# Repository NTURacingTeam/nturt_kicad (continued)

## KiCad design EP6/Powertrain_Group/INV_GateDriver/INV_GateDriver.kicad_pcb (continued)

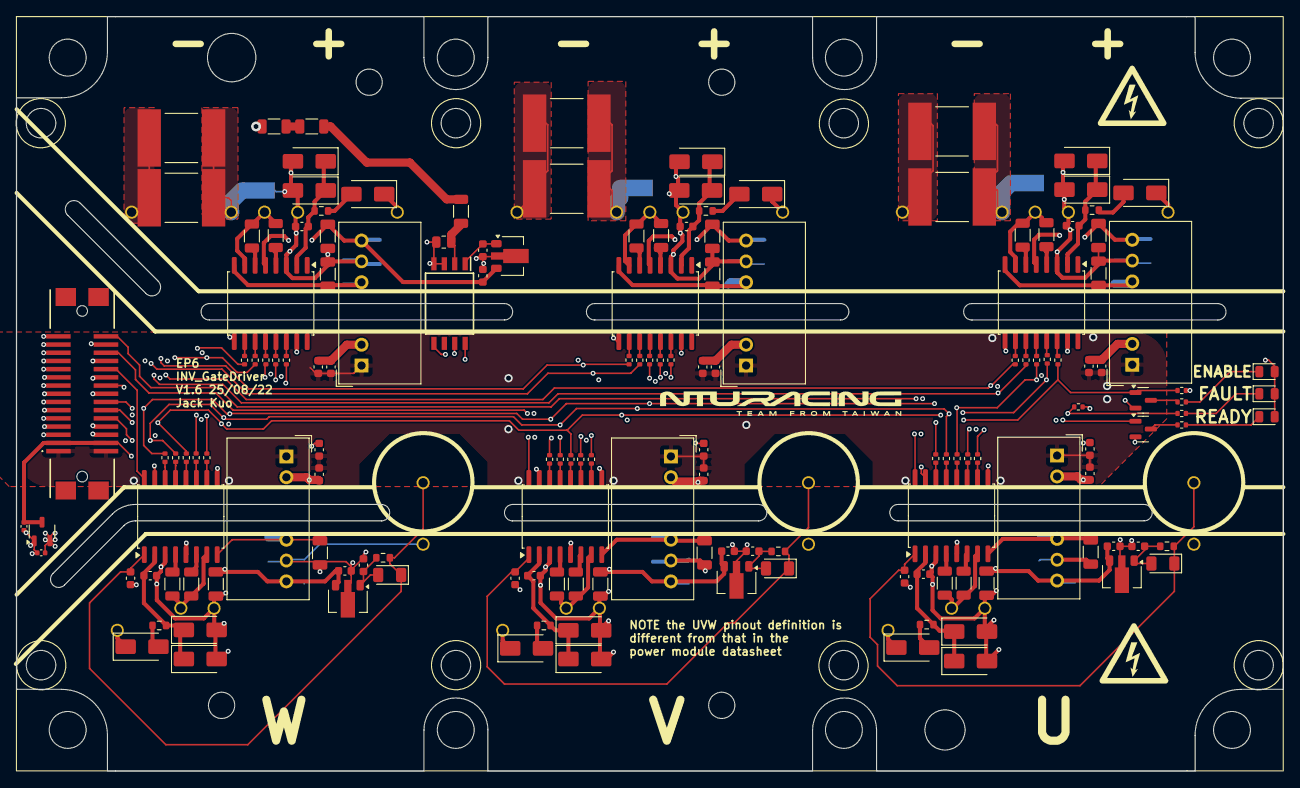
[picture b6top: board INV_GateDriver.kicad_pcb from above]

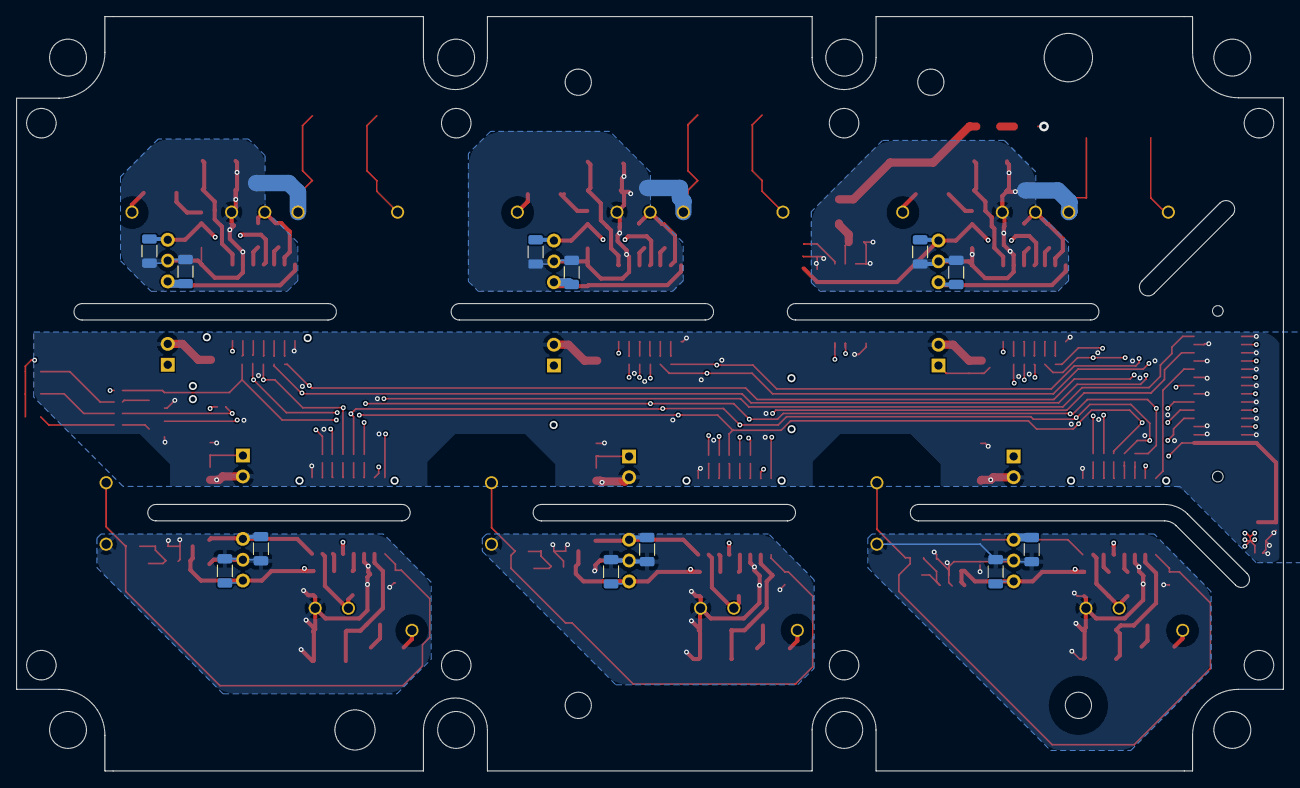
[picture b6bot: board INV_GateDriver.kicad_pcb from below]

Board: 4 copper layers, 154.5 x 92.0 mm, 174 parts (15 on the bottom side), 122 nets.

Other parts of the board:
R17, R18, R24, R25, R28, R29, R35, R36: CRCW080510R0FKEAHP; R_1206_3216Metric

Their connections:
/GateDriverNodeU/G_H: R28.1, R29.2; also elsewhere on the board
/GateDriverNodeU/G_L: R35.1, R36.2; also elsewhere on the board
/GateDriverNodeV/G_H: R17.1, R18.2; also elsewhere on the board
/GateDriverNodeV/G_L: R24.1, R25.2; also elsewhere on the board
unnamed 103: R17.2; also elsewhere on the board
unnamed 104: R18.1; also elsewhere on the board
unnamed 110: R24.2; also elsewhere on the board
unnamed 111: R25.1; also elsewhere on the board
unnamed 117: R28.2; also elsewhere on the board
unnamed 118: R29.1; also elsewhere on the board
unnamed 124: R35.2; also elsewhere on the board
unnamed 125: R36.1; also elsewhere on the board

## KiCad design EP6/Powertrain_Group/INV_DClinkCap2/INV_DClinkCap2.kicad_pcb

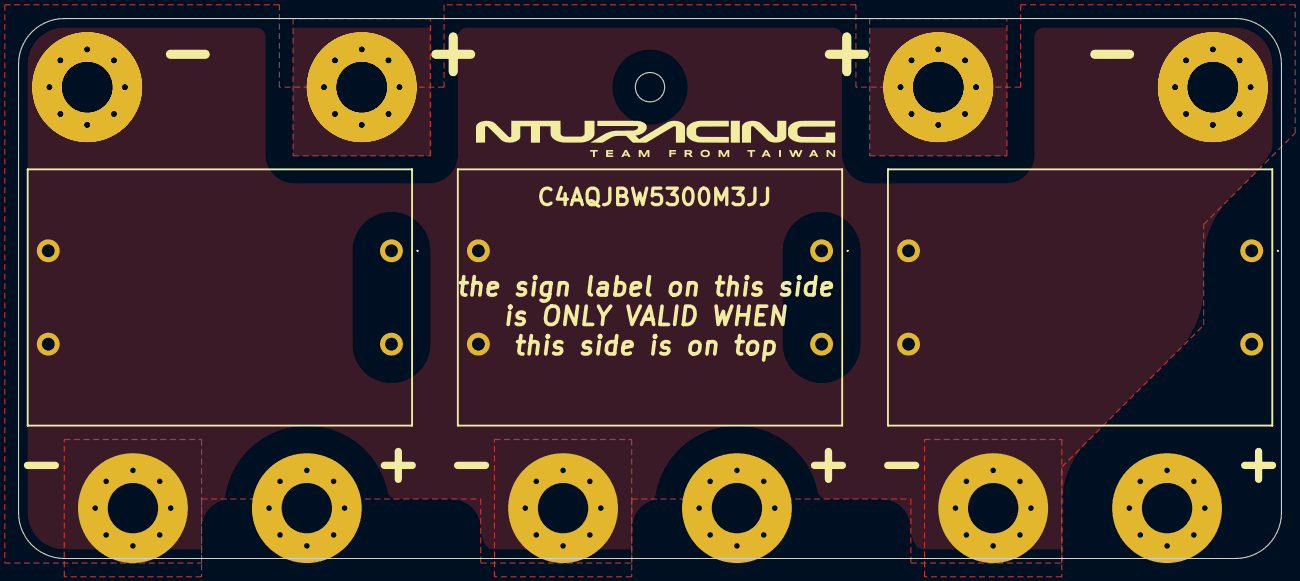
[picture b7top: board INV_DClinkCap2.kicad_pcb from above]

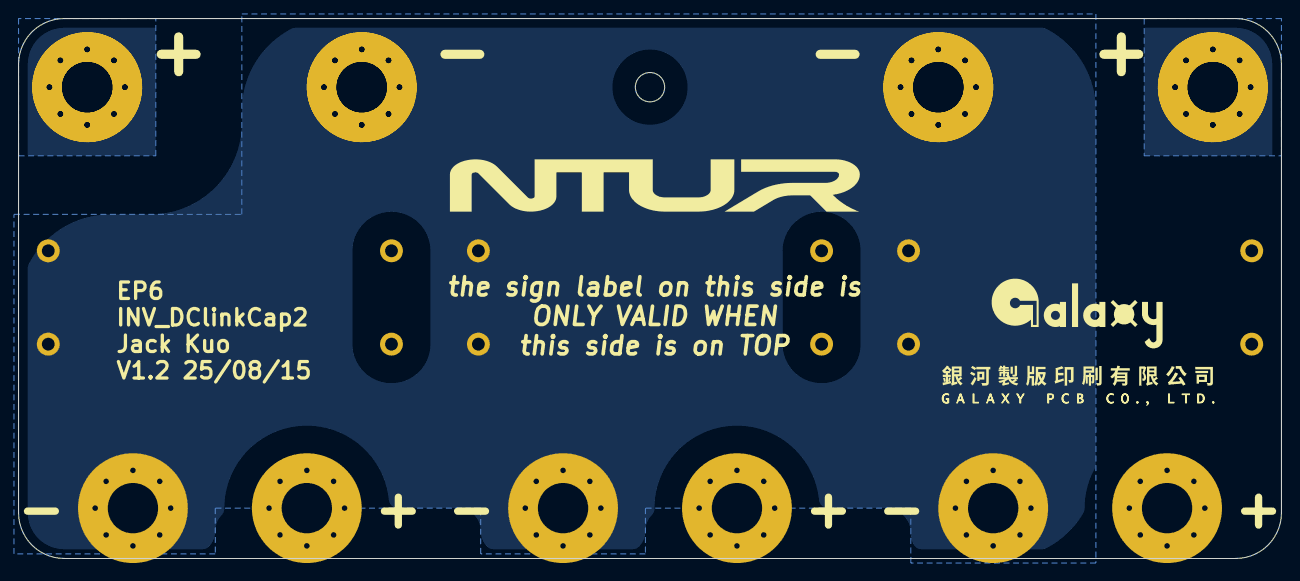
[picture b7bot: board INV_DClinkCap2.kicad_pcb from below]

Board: 2 copper layers, 138.0 x 59.0 mm, 18 parts (7 on the bottom side), 2 nets, no tracks yet.

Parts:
C1, C3, C5: 30µF; C4AQJBW5300M3JJ
H1, H3, H5, H8, H8#2, H10, H10#2: HV-; MountingHole_5.5mm_Pad_Via_15mm_square
H2, H4, H6, H7, H7#2, H9, H9#2: HV+; MountingHole_5.5mm_Pad_Via_15mm_square
H11: MountingHole; MountingHole_3.2mm_M3

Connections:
HV+: C1.1, C3.1, C5.1, H2.1, H4.1, H6.1, H7.1, H7#2.1, H9.1, H9#2.1
HV-: C1.2, C3.2, C5.2, H1.1, H3.1, H5.1, H8.1, H8#2.1, H10.1, H10#2.1

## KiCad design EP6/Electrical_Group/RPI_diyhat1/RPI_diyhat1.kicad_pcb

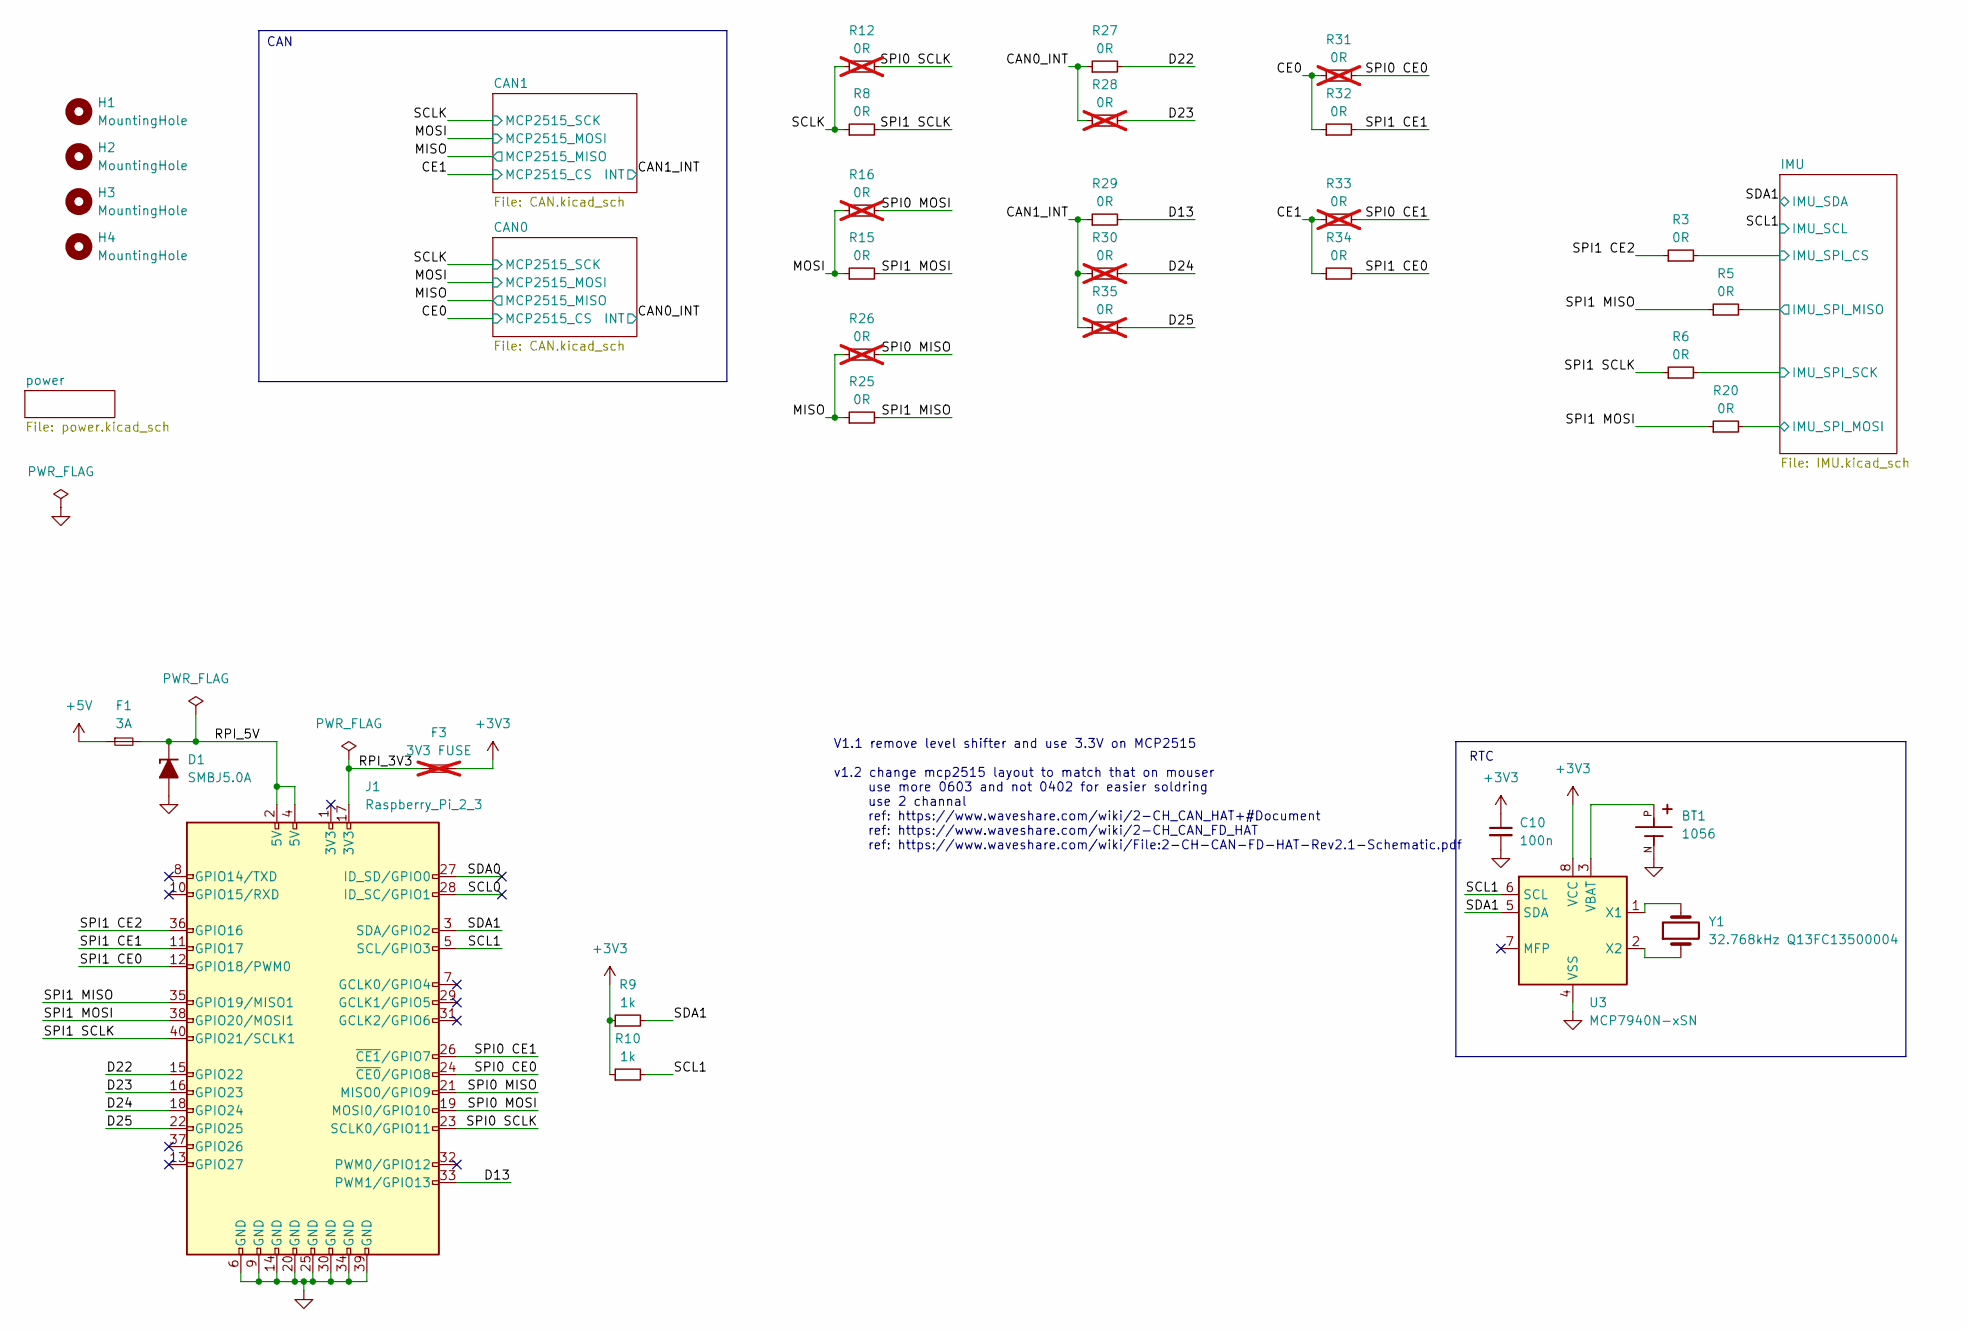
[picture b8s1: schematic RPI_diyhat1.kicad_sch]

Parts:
BT1: 1056; BAT_1056; PARTREV D
C10: 100n; C_0603_1608Metric
D1: SMBJ5.0A; D_SMB
F1: 3A; Fuse_1206_3216Metric
F3: 3V3 FUSE; Fuse_1206_3216Metric; not fitted
H1, H2, H3, H4: MountingHole; MountingHole_2.7mm_M2.5
J1: Raspberry_Pi_2_3; PinSocket_2x20_P2.54mm_Vertical
R3, R5, R6, R8, R15, R20, R25, R27, R29, R32, R34: 0R; R_0603_1608Metric
R9, R10: 1k; R_0603_1608Metric
R12, R16, R26, R28, R30, R31, R33, R35: 0R; R_0603_1608Metric; not fitted
U3: MCP7940N-xSN; SOIC-8_3.9x4.9mm_P1.27mm
Y1: 32.768kHz Q13FC13500004; Crystal_SMD_3215-2Pin_3.2x1.5mm

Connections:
+3V3: C10.1, F3.2, R9.1, R10.1, U3.8 (VCC); also elsewhere on the board
+5V: F1.1; also elsewhere on the board
/CAN0_INT: R27.1, R28.1; also elsewhere on the board
/CAN1_INT: R29.1, R30.1, R35.1; also elsewhere on the board
/CE0: R31.1, R32.1; also elsewhere on the board
/CE1: R33.1, R34.1; also elsewhere on the board
/D13: J1.33 (PWM1/GPIO13), R29.2
/D22: J1.15 (GPIO22), R27.2
/D23: J1.16 (GPIO23), R28.2
/D24: J1.18 (GPIO24), R30.2
/D25: J1.22 (GPIO25), R35.2
/IMU/IMU_SPI_CS: R3.2; also elsewhere on the board
/IMU/IMU_SPI_MISO: R5.2; also elsewhere on the board
/IMU/IMU_SPI_MOSI: R20.2; also elsewhere on the board
/IMU/IMU_SPI_SCK: R6.2; also elsewhere on the board
/MISO: R25.1, R26.1; also elsewhere on the board
/MOSI: R15.1, R16.1; also elsewhere on the board
/RPI_3V3: F3.1, J1.17 (3V3)
/RPI_5V: D1.1 (K), F1.2, J1.2 (5V), J1.4 (5V)
/SCL0: J1.28 (ID_SC/GPIO1)
/SCL1: J1.5 (SCL/GPIO3), R10.2, U3.6 (SCL); also elsewhere on the board
/SCLK: R8.1, R12.1; also elsewhere on the board
/SDA0: J1.27 (ID_SD/GPIO0)
/SDA1: J1.3 (SDA/GPIO2), R9.2, U3.5 (SDA); also elsewhere on the board
/SPI0 CE0: J1.24 (~CE0/GPIO8), R31.2
/SPI0 CE1: J1.26 (~CE1/GPIO7), R33.2
/SPI0 MISO: J1.21 (MISO0/GPIO9), R26.2
/SPI0 MOSI: J1.19 (MOSI0/GPIO10), R16.2
/SPI0 SCLK: J1.23 (SCLK0/GPIO11), R12.2
/SPI1 CE0: J1.12 (GPIO18/PWM0), R34.2
/SPI1 CE1: J1.11 (GPIO17), R32.2
/SPI1 CE2: J1.36 (GPIO16), R3.1
/SPI1 MISO: J1.35 (GPIO19/MISO1), R5.1, R25.2
/SPI1 MOSI: J1.38 (GPIO20/MOSI1), R15.2, R20.1
/SPI1 SCLK: J1.40 (GPIO21/SCLK1), R6.1, R8.2
GND: BT1.N, C10.2, D1.2 (A), J1.6 (GND), J1.9 (GND), J1.14 (GND), J1.20 (GND), J1.25 (GND), J1.30 (GND), J1.34 (GND), J1.39 (GND), U3.4 (VSS); also elsewhere on the board
unnamed: BT1.P, U3.3 (VBAT)
unnamed: U3.1 (X1), Y1.2
unnamed: U3.2 (X2), Y1.1

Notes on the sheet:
RTC
CAN
V1.1 remove level shifter and use 3.3V on MCP2515 v1.2 change mcp2515 layout to match that on mouser use more 0603 and not 0402 for easier soldring use 2 channal ref: https://www.waveshare.com/wiki/2-CH_CAN_HAT+#Document ref: https://www.waveshare.com/wiki/2-CH_CAN_FD_HAT ref: https://www.waveshare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

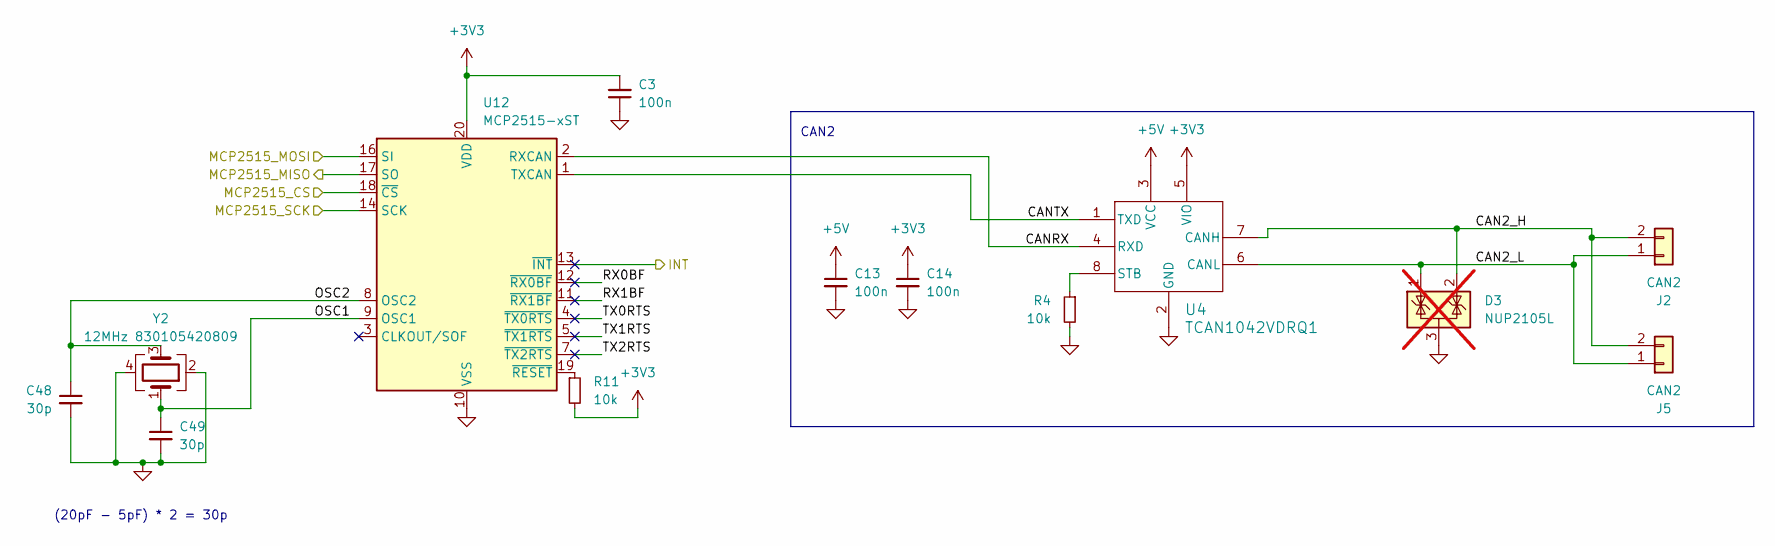
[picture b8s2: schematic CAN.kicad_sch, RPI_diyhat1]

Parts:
C3, C13, C14: 100n; C_0603_1608Metric
C48, C49: 30p; C_0603_1608Metric
D3: NUP2105L; SOT-23; not fitted
J2, J5: CAN2; JST_XH_B2B-XH-A_1x02_P2.50mm_Vertical
R4: 10k; C_0603_1608Metric
R11: 10k; R_0603_1608Metric
U4: TCAN1042VDRQ1; SOIC-8_3.9x4.9mm_P1.27mm
U12: MCP2515-xST; TSSOP-20_4.4x6.5mm_P0.65mm
Y2: 12MHz 830105420809; Crystal_SMD_3225-4Pin_3.2x2.5mm

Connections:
+3V3: C3.2, C14.1, R11.2, U4.5 (VIO), U12.20 (VDD); also elsewhere on the board
+5V: C13.1, U4.3 (VCC); also elsewhere on the board
/CAN1/CAN2_H: D3.2 (K), J2.2, J5.2, U4.7 (CANH)
/CAN1/CAN2_L: D3.1 (K), J2.1, J5.1, U4.6 (CANL)
/CAN1/CANRX: U4.4 (RXD), U12.2 (RXCAN)
/CAN1/CANTX: U4.1 (TXD), U12.1 (TXCAN)
/CAN1/OSC1: C49.1, U12.9 (OSC1), Y2.1
/CAN1/OSC2: C48.1, U12.8 (OSC2), Y2.3
/CAN1/RX0BF: U12.12 (~RX0BF)
/CAN1/RX1BF: U12.11 (~RX1BF)
/CAN1/TX0RTS: U12.4 (~TX0RTS)
/CAN1/TX1RTS: U12.5 (~TX1RTS)
/CAN1/TX2RTS: U12.7 (~TX2RTS)
/CAN1_INT: U12.13 (~INT); also elsewhere on the board
/CE1: U12.18 (~CS); also elsewhere on the board
/MISO: U12.17 (SO); also elsewhere on the board
/MOSI: U12.16 (SI); also elsewhere on the board
/SCLK: U12.14 (SCK); also elsewhere on the board
GND: C3.1, C13.2, C14.2, C48.2, C49.2, D3.3 (A), R4.2, U4.2 (GND), U12.10 (VSS), Y2.2, Y2.4; also elsewhere on the board
unnamed: R4.1, U4.8 (STB)
unnamed: R11.1, U12.19 (~RESET)

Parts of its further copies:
C2, C34, C35: 100n; C_0603_1608Metric
C50, C51: 30p; C_0603_1608Metric
D8: NUP2105L; SOT-23; not fitted
J6, J7: CAN2; JST_XH_B2B-XH-A_1x02_P2.50mm_Vertical
R17: 10k; R_0603_1608Metric
R18: 10k; C_0603_1608Metric
U8: TCAN1042VDRQ1; SOIC-8_3.9x4.9mm_P1.27mm
U13: MCP2515-xST; TSSOP-20_4.4x6.5mm_P0.65mm
Y3: 12MHz 830105420809; Crystal_SMD_3225-4Pin_3.2x2.5mm

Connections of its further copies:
+3V3: C2.2, C35.1, R17.2, U8.5 (VIO), U13.20 (VDD); also elsewhere on the board
+5V: C34.1, U8.3 (VCC); also elsewhere on the board
/CAN0/CAN2_H: D8.2 (K), J6.2, J7.2, U8.7 (CANH)
/CAN0/CAN2_L: D8.1 (K), J6.1, J7.1, U8.6 (CANL)
/CAN0/CANRX: U8.4 (RXD), U13.2 (RXCAN)
/CAN0/CANTX: U8.1 (TXD), U13.1 (TXCAN)
/CAN0/OSC1: C51.1, U13.9 (OSC1), Y3.1
/CAN0/OSC2: C50.1, U13.8 (OSC2), Y3.3
/CAN0/RX0BF: U13.12 (~RX0BF)
/CAN0/RX1BF: U13.11 (~RX1BF)
/CAN0/TX0RTS: U13.4 (~TX0RTS)
/CAN0/TX1RTS: U13.5 (~TX1RTS)
/CAN0/TX2RTS: U13.7 (~TX2RTS)
/CAN0_INT: U13.13 (~INT); also elsewhere on the board
/CE0: U13.18 (~CS); also elsewhere on the board
/MISO: U13.17 (SO); also elsewhere on the board
/MOSI: U13.16 (SI); also elsewhere on the board
/SCLK: U13.14 (SCK); also elsewhere on the board
GND: C2.1, C34.2, C35.2, C50.2, C51.2, D8.3 (A), R18.2, U8.2 (GND), U13.10 (VSS), Y3.2, Y3.4; also elsewhere on the board
unnamed: R18.1, U8.8 (STB)
unnamed: R17.1, U13.19 (~RESET)

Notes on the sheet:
(20pF - 5pF) * 2 = 30p
CAN2

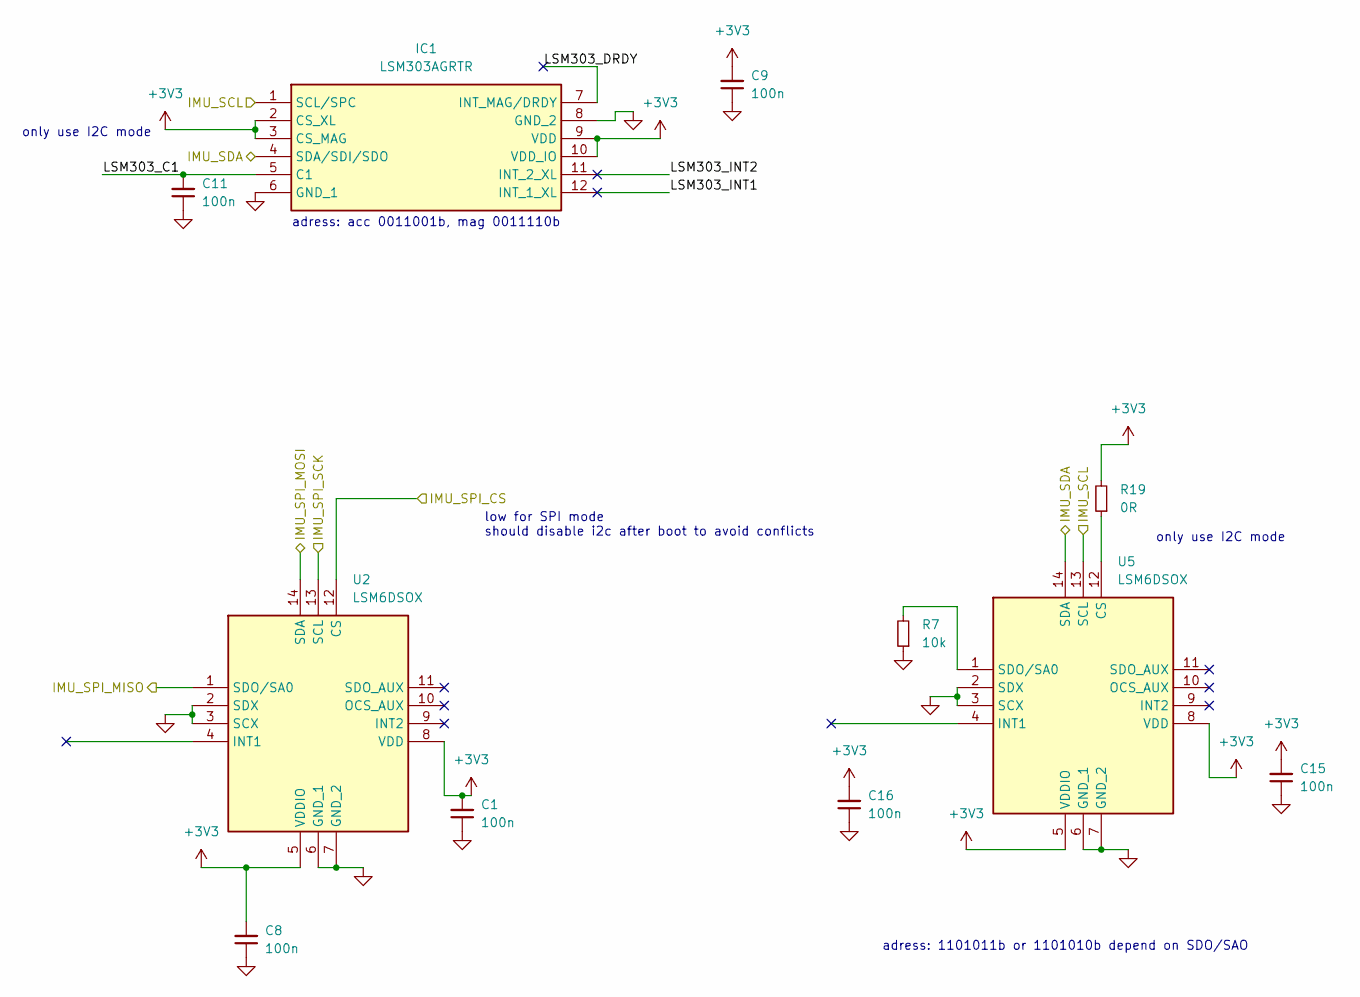
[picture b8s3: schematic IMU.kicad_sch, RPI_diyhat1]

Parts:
C1, C8, C9, C11, C15, C16: 100n; C_0402_1005Metric
IC1: LSM303AGRTR; LGA-12_2x2mm_P0.5mm; Mouser Part Number 511-LSM303AGRTR
R7: 10k; R_0402_1005Metric
R19: 0R; R_0402_1005Metric
U2, U5: LSM6DSOX; LGA-14_3x2.5mm_P0.5mm_LayoutBorder3x4y; Mouser Part Number 511-LSM6DSOXTR

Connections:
+3V3: C1.2, C8.2, C9.2, C15.2, C16.2, IC1.2 (CS_XL), IC1.3 (CS_MAG), IC1.9 (VDD), IC1.10 (VDD_IO), R19.2, U2.5 (VDDIO), U2.8 (VDD), U5.5 (VDDIO), U5.8 (VDD); also elsewhere on the board
/IMU/IMU_SPI_CS: U2.12 (CS); also elsewhere on the board
/IMU/IMU_SPI_MISO: U2.1 (SDO/SA0); also elsewhere on the board
/IMU/IMU_SPI_MOSI: U2.14 (SDA); also elsewhere on the board
/IMU/IMU_SPI_SCK: U2.13 (SCL); also elsewhere on the board
/IMU/LSM303_C1: C11.2, IC1.5 (C1)
/IMU/LSM303_DRDY: IC1.7 (INT_MAG/DRDY)
/IMU/LSM303_INT1: IC1.12 (INT_1_XL)
/IMU/LSM303_INT2: IC1.11 (INT_2_XL)
/SCL1: IC1.1 (SCL/SPC), U5.13 (SCL); also elsewhere on the board
/SDA1: IC1.4 (SDA/SDI/SDO), U5.14 (SDA); also elsewhere on the board
GND: C1.1, C8.1, C9.1, C11.1, C15.1, C16.1, IC1.6 (GND_1), IC1.8 (GND_2), R7.1, U2.2 (SDX), U2.3 (SCX), U2.6 (GND_1), U2.7 (GND_2), U5.2 (SDX), U5.3 (SCX), U5.6 (GND_1), U5.7 (GND_2); also elsewhere on the board
unnamed: R19.1, U5.12 (CS)
unnamed: R7.2, U5.1 (SDO/SA0)

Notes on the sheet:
only use I2C mode
adress: acc 0011001b, mag 0011110b
low for SPI mode should disable i2c after boot to avoid conflicts
adress: 1101011b or 1101010b depend on SDO/SAO

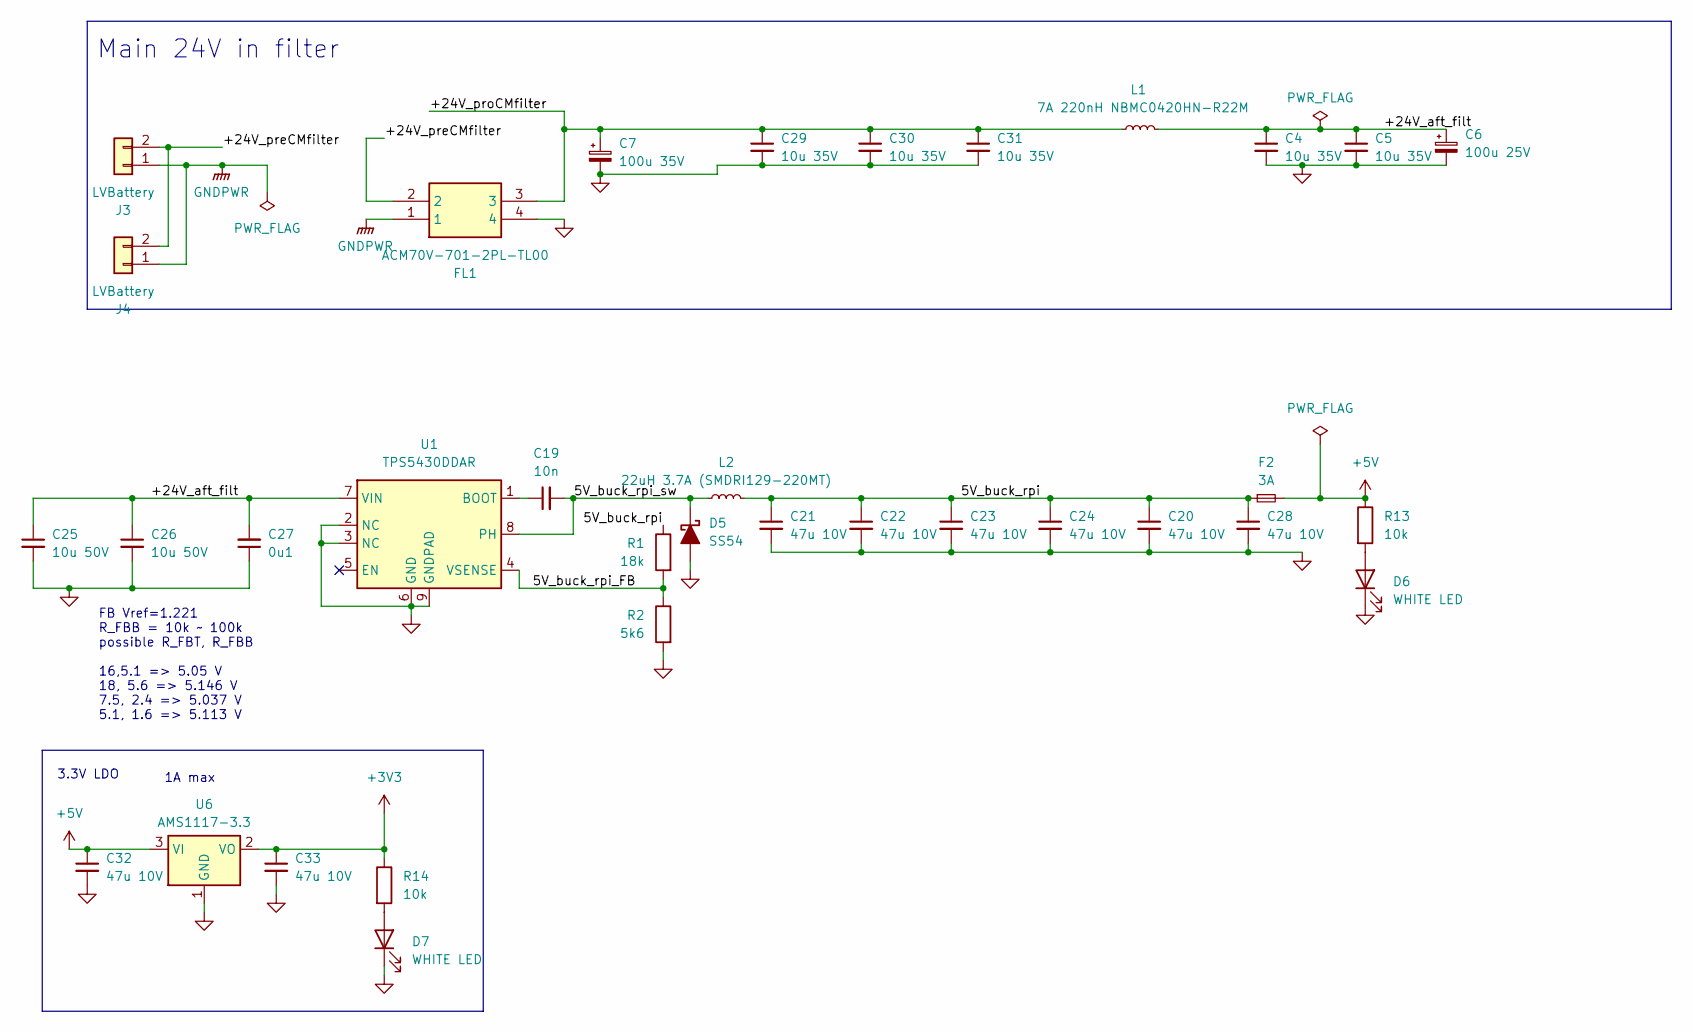
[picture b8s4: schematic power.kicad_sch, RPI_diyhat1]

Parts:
C4, C5, C29, C30, C31: 10u 35V; C_1206_3216Metric
C6: 100u 25V; CP_Radial_D6.3mm_P2.50mm
C7: 100u 35V; CP_Radial_D6.3mm_P2.50mm
C19: 10n; C_0603_1608Metric
C20, C21, C22, C23, C24, C28, C32, C33: 47u 10V; C_1206_3216Metric
C25, C26: 10u 50V; C_1206_3216Metric
C27: 0u1; C_0603_1608Metric
D5: SS54; D_SMA
D6, D7: WHITE LED; LED_0603_1608Metric
F2: 3A; Fuse_1206_3216Metric
FL1: ACM70V-701-2PL-TL00; ACM70V7012PLTL00; Mouser Part Number 810-ACM70V7012PLTL00
J3, J4: LVBattery; JST_XH_B2B-XH-A_1x02_P2.50mm_Vertical
L1: 7A 220nH NBMC0420HN-R22M; L_Ferrocore_DLG-0403
L2: 22uH 3.7A (SMDRI129-220MT); L_Bourns_SRR1260
R1: 18k; R_0603_1608Metric
R2: 5k6; R_0603_1608Metric
R13, R14: 10k; R_0603_1608Metric
U1: TPS5430DDAR; TI_SO-PowerPAD-8_ThermalVias
U6: AMS1117-3.3; SOT-223-3_TabPin2

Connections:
+3V3: C33.1, R14.1, U6.2 (VO); also elsewhere on the board
+5V: C32.1, F2.2, R13.1, U6.3 (VI); also elsewhere on the board
/power/5V_buck_rpi: C20.1, C21.1, C22.1, C23.1, C24.1, C28.1, F2.1, L2.2, R1.1
/power/5V_buck_rpi_FB: R1.2, R2.1, U1.4 (VSENSE)
/power/5V_buck_rpi_sw: C19.2, D5.1 (K), L2.1, U1.8 (PH)
/power/+24V_aft_filt: C4.1, C5.1, C6.1, C25.1, C26.1, C27.2, L1.2, U1.7 (VIN)
/power/+24V_preCMfilter: FL1.2, J3.2, J4.2
/power/+24V_proCMfilter: C7.1, C29.1, C30.1, C31.1, FL1.3, L1.1
GND: C4.2, C5.2, C6.2, C7.2, C20.2, C21.2, C22.2, C23.2, C24.2, C25.2, C26.2, C27.1, C28.2, C29.2, C30.2, C31.2, C32.2, C33.2, D5.2 (A), D6.1 (K), D7.1 (K), FL1.4, R2.2, U1.2 (NC), U1.3 (NC), U1.6 (GND), U1.9 (GNDPAD), U6.1 (GND); also elsewhere on the board
GNDPWR: FL1.1, J3.1, J4.1
unnamed: D6.2 (A), R13.2
unnamed: D7.2 (A), R14.2
unnamed: C19.1, U1.1 (BOOT)

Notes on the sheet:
3.3V LDO
FB Vref=1.221 R_FBB = 10k ~ 100k possible R_FBT, R_FBB 16,5.1 => 5.05 V 18, 5.6 => 5.146 V 7.5, 2.4 => 5.037 V 5.1, 1.6 => 5.113 V
1A max
Main 24V in filter

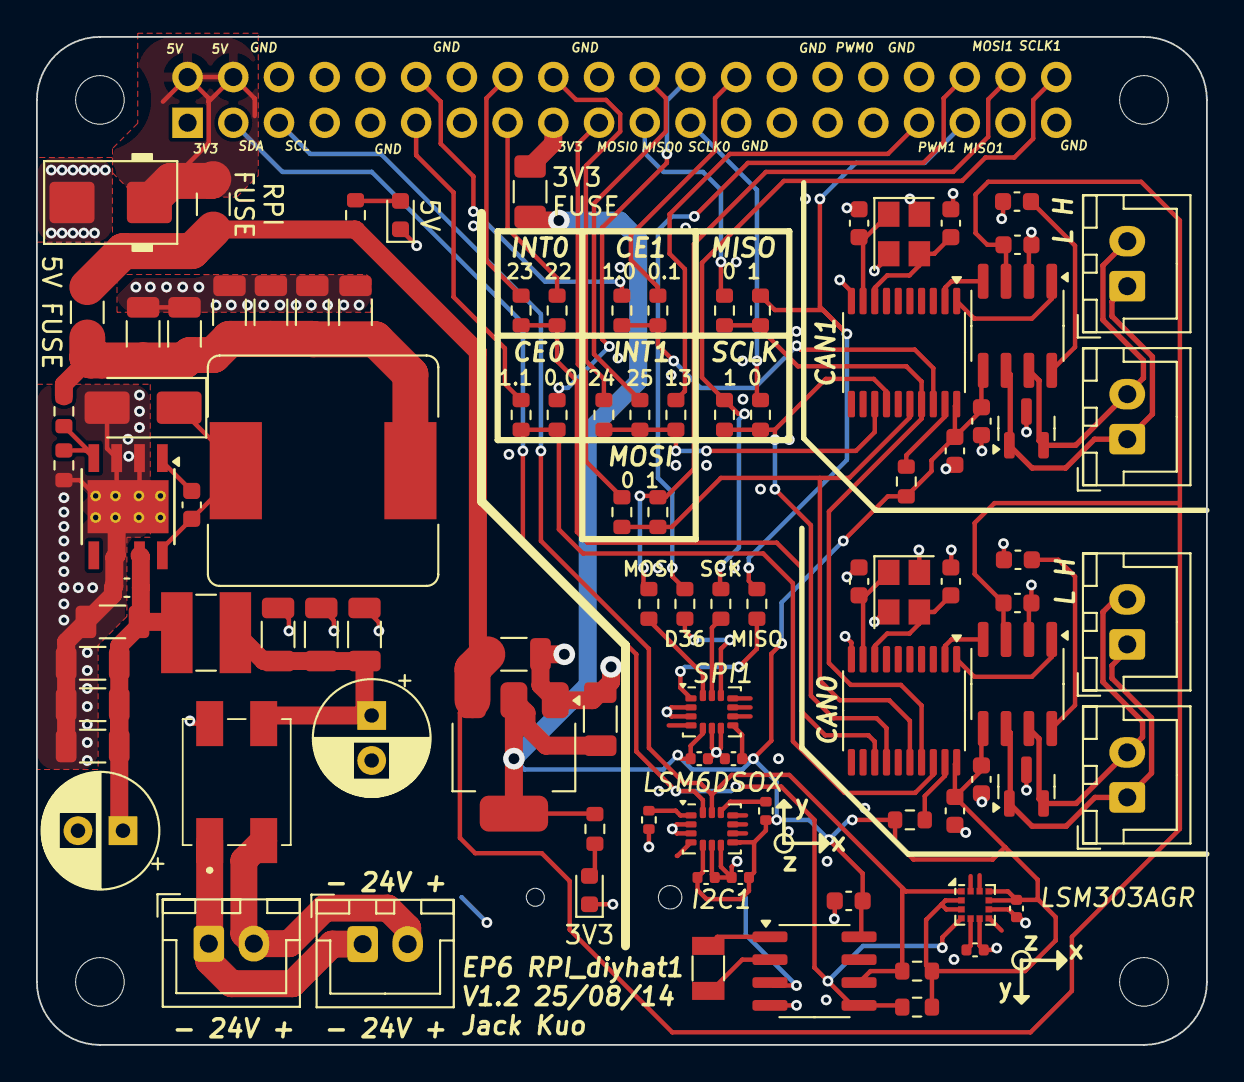
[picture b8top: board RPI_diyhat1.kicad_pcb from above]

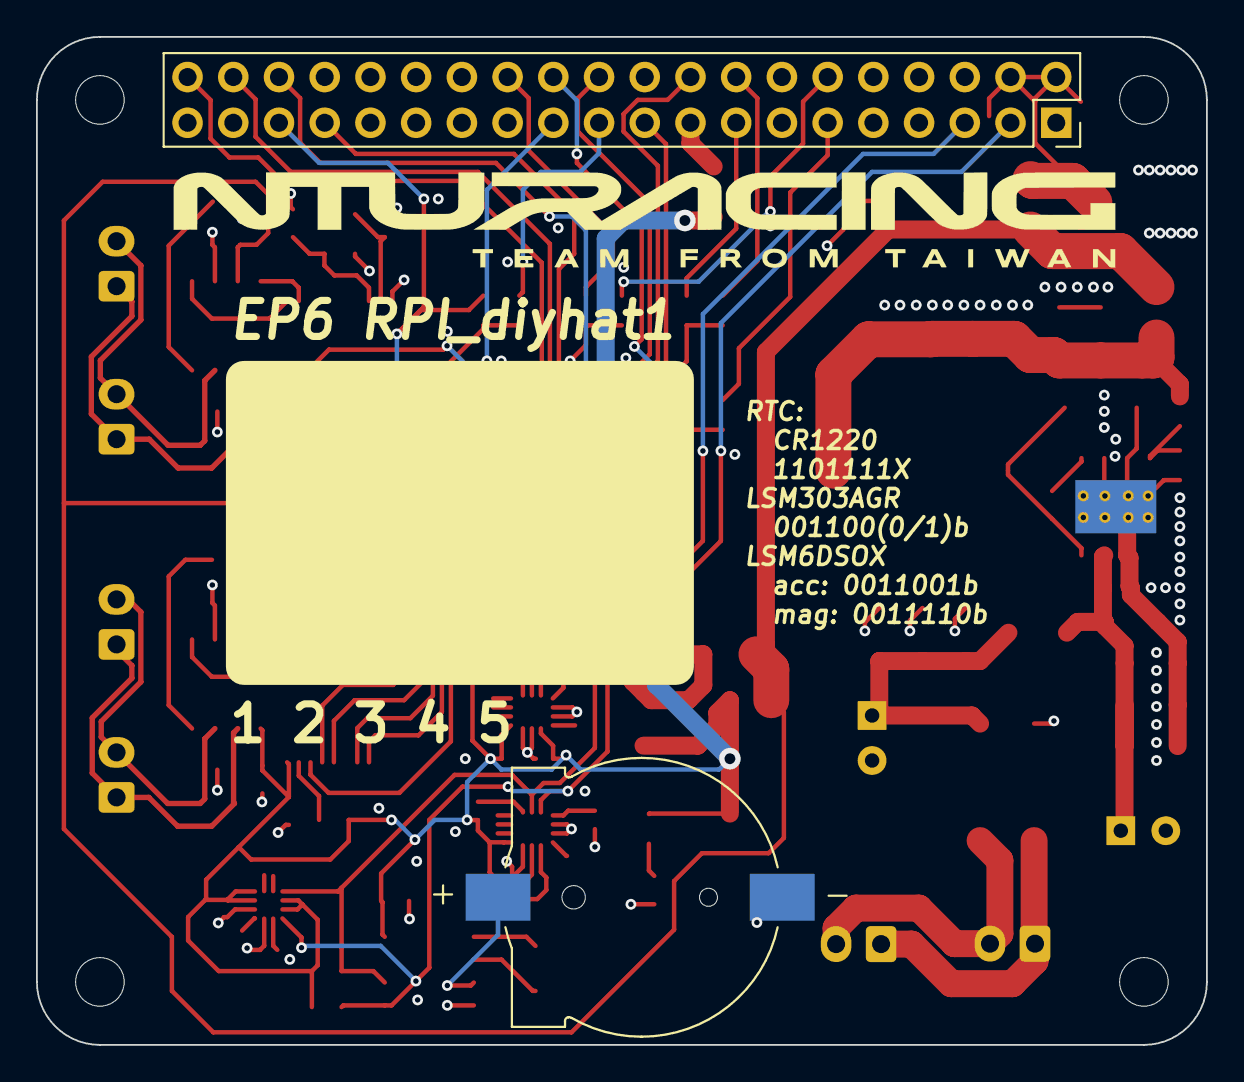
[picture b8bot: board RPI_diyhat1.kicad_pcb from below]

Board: 4 copper layers, 65.0 x 56.0 mm, 104 parts (2 on the bottom side), 66 nets.

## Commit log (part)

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2023-08-07 add project libraries
    lagacy
2023-08-07 add precharge
    lagacy
2023-08-07 add HV box
    legacy
2023-08-07 add front box nucleo
    legacy
2023-08-07 Create README.md for EP4
2023-08-07 add zip to gitignore
2023-08-08 add mounting hole to rearbox nucleo
2023-08-08 use online library for frontbox
    replaced: TEN_40-2411WIE, CTM1051AM
2023-08-08 apply net class on frontbox
    power class with 5 mm track width for +5V and VCC
2023-08-13 rename components schematic sheet
2023-08-13 in frontbox nucleo use wider track on gnd
2023-11-01 add EP5 7-segment testing for electrical group
    7 segment for dashboard
2023-11-17 driverless car middle board v2 exported GBR, PDF
2023-11-27 Update and rename EP5/Electrical Group/NTUR 7-segment testing/electronics.kicad_sch to EP5/Electrical Group/NTUR 7-segment testing/rearbox/electronics.kicad_sch
    move the file
2023-11-28 update driverless car mid board 23/11/22 rev3
2023-11-28 fix rearbox_nucleo_1 folder location
    and add project library for ep5
2023-12-07 Add files via upload
    upload schematic
2024-01-01 add 3 boards for dashboard, ver 1 all done
    pdf included
    new library included
2024-01-02 add dashboard single board version
    using 4 layer PCB
    use nucleo G431KB
    hope to use raw MC, and not nucleo
    with pdf
2024-02-22 update rear box nucleo
    but only connector symbols
2024-03-03 EP4 front box nucleo super minor update
2024-03-03 dashboard update left board to latest design
    left board is DIYbox board 2
2024-03-08 update rearbox nucleo
2024-03-09 update rearbox nucleo 1
    mainly make a plane for GNDPWR
2024-03-10 update rearbox nucleo 1 (mainly switch debounce)
2024-03-10 1st dashboard screen board done
    and minor pin modification on dashboard left board
2024-03-11 modify rearbox left connector board for face upwards
    (in order jst connector face upward )
2024-03-11 add rearbox powerboard (only schematic)
2024-03-13 minor update on power board
2024-03-20 update boards in rear box after Tsou's review
2024-03-21 update all boards after Tsou's second review
2024-03-22 update rearbox nucleo hat for RPI CAN
2024-03-22 add Mr. Kang recommended CAN transciever to library
2024-03-22 update power board for improved F silkscreen
2024-04-08 update dashboard board2 and power board
2024-06-24 add several parts to EP5 library samacSys
    CR1220 battery holder
    LMR66430R5RXBR
    MSD4A
    SOP65P640X120
    TO254P469X1042X1930
2024-06-24 version 2 for rearbox nucleo 1
    abandon power isolation
    use bulk head connectors instead of JST XH
    add sd card
    add 7segment * 2
    etc.
2024-07-04 CANbus connector board V1.0
    mainly for inverter
2024-07-04 update dashboard board 1 & 2 to V2.0 to cancel isolation and use IDC socket
2024-07-04 update rearbox Nucleo hat to V2.0 to cancel isolation and use IDC socket
2024-07-04 update LVBMS to V2.0, more connectors
2024-07-04 update Rpi hat V1.0
    included function
    RTC
    CAN
    2 IMUs
    some buttons and indicators from GPIO
2024-07-21 update LVBMS to V2.1
    fix XT60 reverse
    fix show current should be at ground
    fix lack of labeling
2024-07-21 update dashboard board 1 to v2.1
    fix RTD button light, GND should be 5V, and signal using open drain to control
2024-07-21 udpate library
2024-07-21 updated dashboard board 2 to V3.0
    change buck converter
    change CAN transceiver
    skip pins for zephyr VCP shell
    use NRST for one of the buttons
    add some LEDs
2024-07-22 update rearbox nucleo hat to V3.1
    use buck converter as current source and rather than voltage source
    add 24v voltage and current measurement
2024-07-26 update power board for kicad8
2024-08-05 update dashboard board 2 to v3.0 again
2024-08-07 update dashboard 2 to V4.0
    using stm32H56RG
    use JTAG
    use USB for DFU
    ignore front wheel speed hall sensor
2024-08-07 update LVBMS to V2.1
    mainly update show current connector to ground
2024-08-07 add new board (for rear box VCU+power board)
    use STM32H562VG
2024-10-12 add rearbox_VCUandPower to EP5
2024-10-12 add rearbox_nucleo_1_V3.0bak to EP5
2024-10-12 update rearbox_left_connector to V2.2 in EP5
2024-10-12 create dashboard 2 V3 (backup) for EP5
2024-10-12 update git ignore
2024-10-12 add readme for EP5
    mainly write about library setting
2024-10-12 update library for EP6
2024-10-12 create Potentiometer2Current in EP6
2024-10-12 create APPS_ROT_POT_onboard in EP6
2024-10-12 create APPS_ROT_POT_onboard_XTR11x in EP6
2024-10-12 create 6s_BMS in EP6
2024-10-14 update 6S_BMS schematic, for FET and Balancing
    use highside FET for charge and discharge switch
    and use chip for balance rather than MCU
2024-10-15 update 6S_BMS schematic and a little layout
2024-10-24 create and update HVB_LV1 to V1.0 for EP6 powertrain
    detailed silkscreen labeling awaiting
    layout adjustment awaiting
2024-10-24 add 4 SVGs to EP6
    Galexy logo * 2
    high voltage * 1
    NTURacing logo * 1
2024-10-25 6S BMS sch cleanup
2024-10-25 fix net ties
2024-10-25 added 3d model for cell pack and xt60pw connectors
2024-10-26 front panel board connectors
2024-10-27 fix net ties and net classes
2024-10-27 added hvb front panel
2024-10-27 update some EP6 footprint library 3dshape path
2024-10-27 update 6s front panel
2024-10-30 added level shifter
2024-11-01 added reset buttons, fix errors
2024-11-02 add ACC_HVLV1
    initial version of the schematic done
    also update EP6 nturt_kicad_lib symbol for relay
2024-11-03 edit VCU: add USBHS and adjust IDC connector pinout
2024-11-05 updated cell pack model
2024-11-05 Updated footprint libraries
2024-11-07 replace MCU with STM32H7431
2024-11-08 replace parrallel screen with SPI in VCU PCB
2024-11-11 upload EP5 powertrain boards from local
    ├───BatteryBox
    │ ├───BMS_MASTER_STM32F103C8
    │ ├───BMS_Slave_V1(ADBMS1818)
    │ ├───Connector_Board
    │ ├───Indicator
    │ └───PreCharge
2024-11-15 update library
2024-11-15 add INV_MainBoard_STM32
2024-11-17 batch update for JLCPCB 241117
    6SBMS
    ACC_HVLV1
    INV_CurrentSense2
    INV_CurrentSense3
    DClinkCap1
    INV_MainBoard_STM32
2024-11-21 finished electrical routing in VCU
2024-11-21 add silkscreen on VCU PCB
2024-11-24 VCU snapshot
2024-11-27 VCU layout done
2024-11-30 update EP6 VCU
    minor update:
    add buzzer indicator light
    fix 2 unrouted
    add some return path GND via
    change some silkscreen
    update name and date and version on pcb
2024-11-30 VCU swapped parts, optimized routing and silkscreen
2024-12-01 HVBLV1 cleaner but not necessarily better layout
2024-12-02 HVLV1 added vias, optimized layout
2024-12-05 add and update DEVboard1 to V1.0
    include 5V buck
    stlink bluepill
2024-12-06 add DEV_BLDC and update library
2024-12-23 ACC_BMSslave pcb priliminary layout
2025-01-15 ACC_BMSslave fix routing issue (split input connector)
2025-01-15 ACC_BMSslave fix routing issue (joint input connector)
2025-01-17 ACC_BMSslave optimise layout, added silk
2025-01-18 ACC_BMSslave snapshot
2025-02-13 update EP6 library
2025-02-13 update INV_GateDriver to V1.0 (TBC)
    B2B connector pin out not well defined yet
2025-02-24 [BMSslave] slave board done, connector board very not
2025-02-26 update INV_GateDriver to V1.3 again
    only add some description on schematic and change voltage divider resistance
2025-02-27 update library for SD card slot
2025-02-28 update INV_GateDriver to V1.4
    mainly change iso DCDC to 1503
    change RGon high
    add some text in sch
2025-02-28 [BMSslave] fix silk, added numbers
2025-03-01 update INV_MotorTempIso to V1.1 again
    only slightly change for one via is on pad and wound charge extra for JLCPCB
2025-03-01 update INV_MainBoard_STM32 to V2.1
    update for JLCPCB, include change in 1.65 Vref and some name change for easier JLCPCBA BOM selection
2025-03-04 update INV_MotorTempIso to V1.1 again
    change upper voltage divider resistance to 4k7 to make output voltage lower than 2V
2025-03-06 update INV_PhaseIsense to V1.1
    offset connector to mainboard by 6 mm to better match power module
2025-03-07 update VCU to V2.0 again
    pinout fix mainly due to DMA constraints
2025-03-07 [BMSslave_connector] slight adjustment
2025-03-11 update INV_CONN2 to V1.1
    change temp pinout to match encoder pinout
2025-03-11 update HVB_TSMP_ResCon to V1.0 again
    fix mirrored silkscreen
2025-03-11 update INV_MainBoard_STM32 to V2.1 again
    fix PCB file title block committed last time
2025-03-18 update ACC_HVLV1 to V2.0
    fix some small problem about part placement inside ACC
2025-04-27 [6S_BMS] version 2
2025-04-27 [6S_BMS] v2 added button a b and status led and reset
2025-05-04 add STlink V1.0 to electrical Group
2025-05-04 update PWRboard1 to V1.0 again
    remove unused file and change a file with untitled name to normal
2025-05-04 add Adaptor_USB (V1.0)
2025-05-04 update INV_CONN1 to V1.1
    fix L-coded footprint mistake
2025-05-04 udpate ACC_HVLV1 to V2.1
    fix pre-charge mistake (the high side is connected to HV+ and HV-, HV- is wrong. It should be PACK+)
2025-05-04 add Adaptor_FPC10P (V1.0)
2025-05-08 update IMU_DIY to V1.1
    change to 4 layer
    change layout
    change a little sch
2025-05-08 update STlink to V1.2
    only add fillet
2025-05-10 update ACC_HVLV1 to V2.2
    shrink size to 80*100
2025-05-11 update INV_CONN1 to V1.3
    swap CAN JST XH with DB-9 CAN connector
2025-05-11 update Adaptor_RJ45 to V1.1
    change to shielded RJ45
2025-05-11 update panelGalexy250509_2 to V1.0
    2 layer boards panel
2025-05-16 [BMSslave] update layout
2025-05-16 [BMSslace] Finished version 3.0
2025-05-16 [BMSslave] added mux pins pullup
2025-05-16 [BMSslave] modified graphics
2025-05-18 [6S_BMS] revert to 91fc6f8
2025-05-21 HVB_LV1 update to V3.1
    V3.1 change to HV connector to JST 2.0 mm
    change power light to white
    add some RC filter to BSPD
    use CV buck instead of PWM dimmer + current control buck
    make RTML voltage not adjustable (12V)
    switch to 0805 for some LED
2025-05-30 add TL_TSSI (V1.0)
2025-06-29 update Adaptor_FPC10P to V1.1
    V1.1 move two conns away for 5mm (hard to solder when that close)
2025-06-29 update HVB_CONN1 to V1.1
    V1.1 change TSSI_RTML connector pinout to match 6p connector (5->6, 6->7)
    change dash SB light power source
    change reset button connector to JST 2.0
2025-06-29 update HVB_HVLV_1 to V2.2
    V2.2 remove discharge relay
2025-06-29 update TL_TSSI to V1.2
    V1.2 change mounting hole configureation
    (including removing middle hole and use M2 on 4 corner)
    increase LED count fron 3*2 to 6*2
2025-06-29 add MOT_EncoderRotor V1.0
2025-06-29 udpate VCU to V3.0
    V3.0 move mounting point out a little
    remove HSUSB
    remove brake light
    change conn pinout to match dashboard V1.0
    add CAN2
    add some LEDs
2025-06-29 update ACC_BMSmaster to V3.1
    V3.1 add boot0 button
2025-06-29 Update nturt_kicad_lib.kicad_sym
    APS6404L-3SQ
2025-07-10 update VCU
    no version change
    just update for some modification on schematic after JLCPCBA part selection
2025-07-10 add INV_Diff2Single V1.0
2025-07-10 update library
    SMBJ5.0A
    LSF0204DPWR
2025-07-10 add panelGalexy250630_0\panelGalexy250630_0
2025-07-10 update ACC_HVLV1
    just 500R -> 510R
2025-08-14 [INV_DClinkCap2] update to V1.1
    V1.1 fix edge will overlap power module and has to be cut of problem
    fix different from cad DC bus connection point (reversed)
    use bigger pad for cap soldering
    use 3mm clearance
2025-10-18 create EP7 folder
2025-10-18 added VCU_CM5 and its libraries
2025-10-18 Revise README for path variables and 3D model setup
    Updated the README to improve clarity on configuring path variables and libraries, and added instructions for adding 3D models.
2025-10-18 VCU_CM5 initial floorplan
2026-02-01 update gitignore
2026-02-01 update BMSslave
